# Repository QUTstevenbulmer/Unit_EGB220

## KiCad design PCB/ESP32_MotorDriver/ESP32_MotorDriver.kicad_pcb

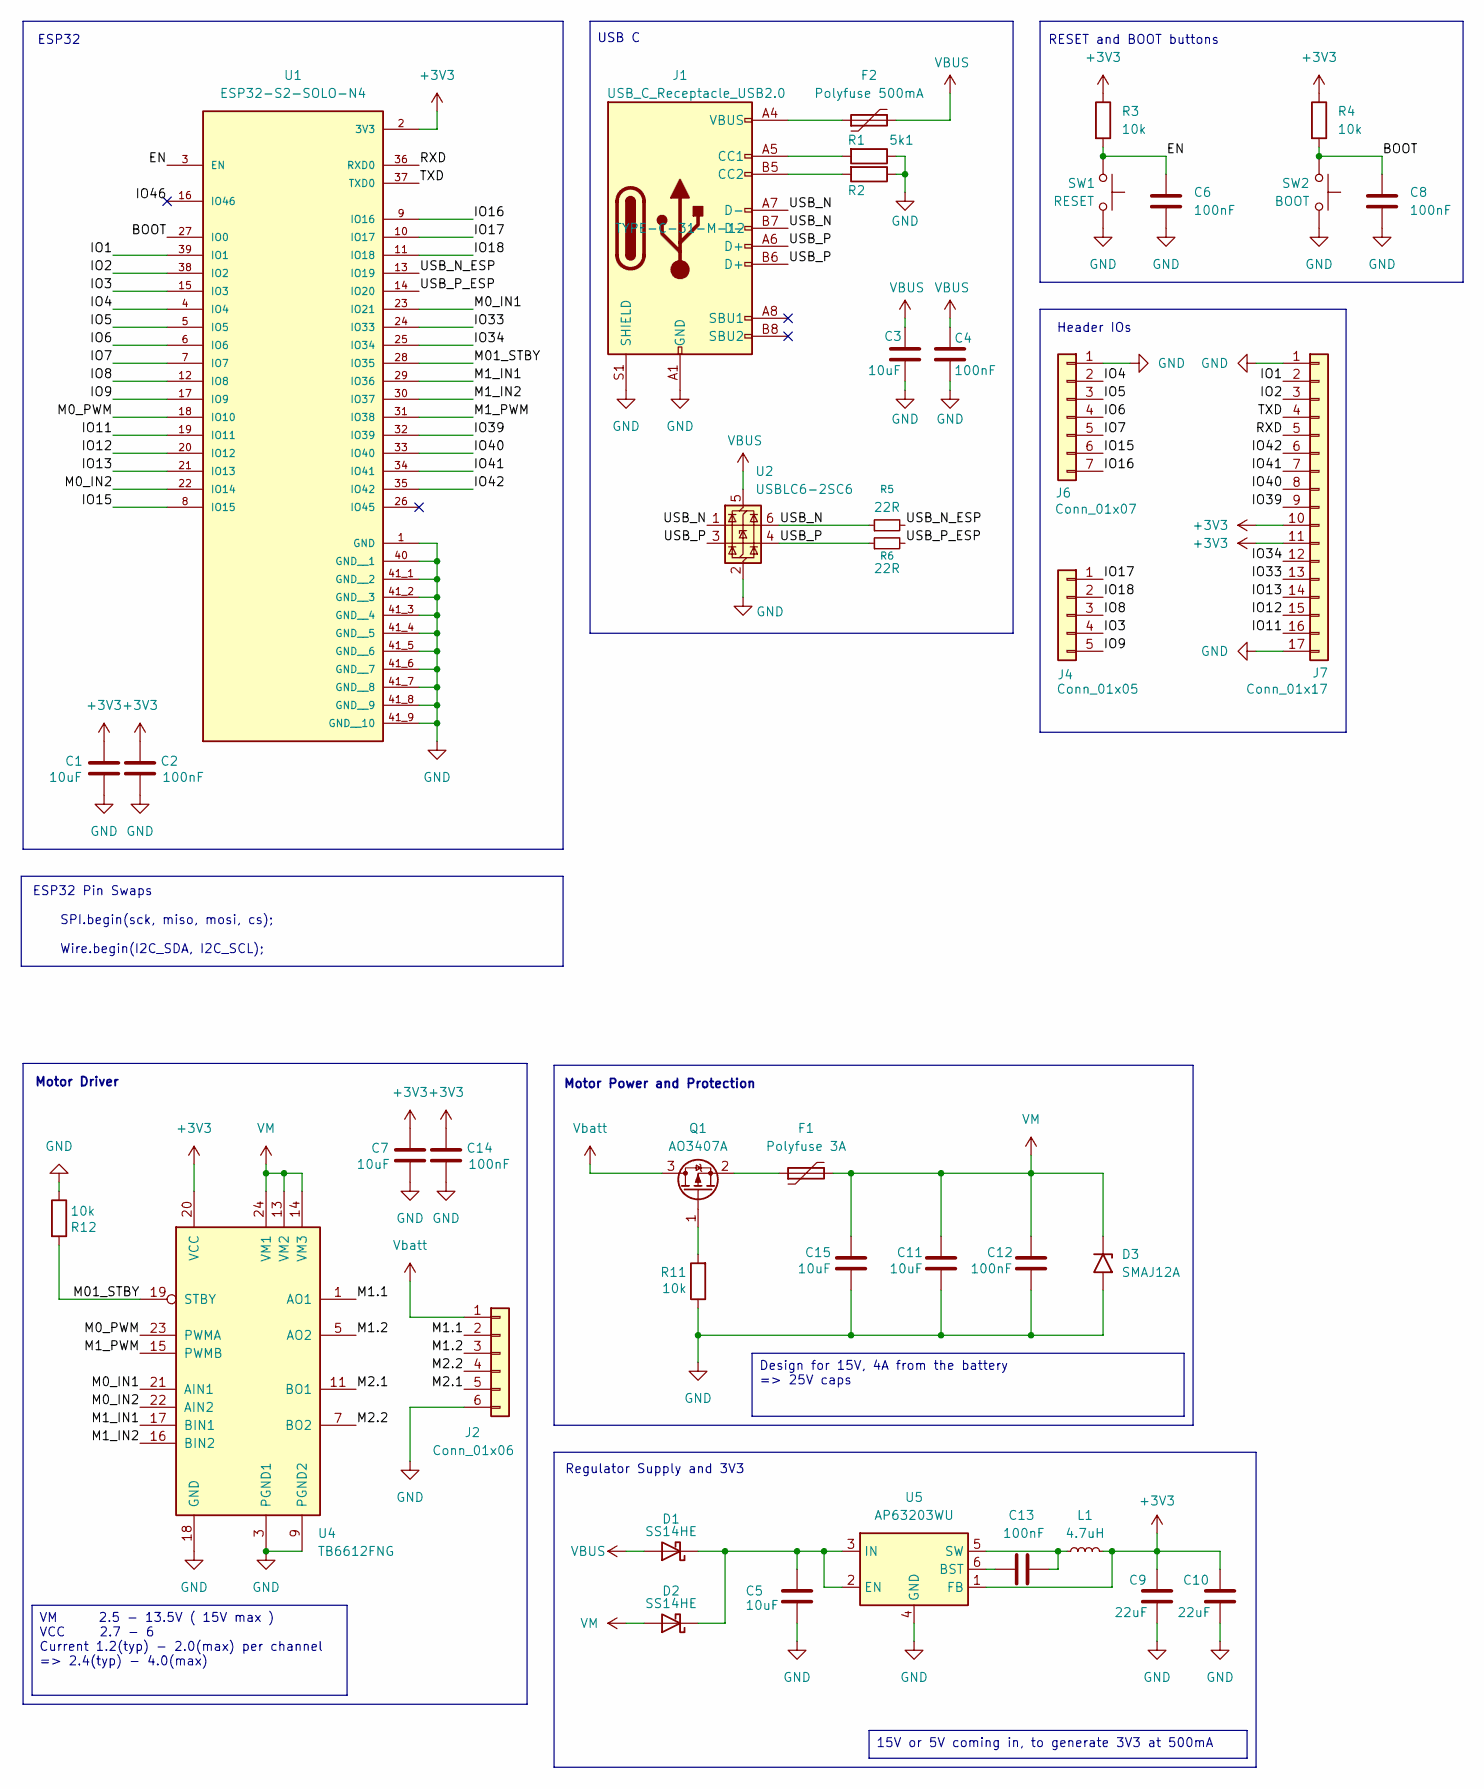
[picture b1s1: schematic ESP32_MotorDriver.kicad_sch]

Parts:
C1, C5, C7, C15: 10uF; C_0805_2012Metric_Pad1.18x1.45mm_HandSolder
C2, C6, C8, C14: 100nF; C_0402_1005Metric_Pad0.74x0.62mm_HandSolder
C3: 10uF; C_0805_2012Metric_Pad1.18x1.45mm_HandSolder; LCSC Part # C15850
C4: 100nF; C_0402_1005Metric_Pad0.74x0.62mm_HandSolder; LCSC Part # C15850
C9, C10: 22uF; C_0805_2012Metric_Pad1.18x1.45mm_HandSolder
C11: 10uF; C_0805_2012Metric_Pad1.18x1.45mm_HandSolder; LCSC PN C3902158
C12, C13: 100nF; C_0402_1005Metric_Pad0.74x0.62mm_HandSolder; LCSC PN C105882
D1, D2: SS14HE; D_SOD-323HE_SS14HE
D3: SMAJ12A; D_SMA
F1: Polyfuse 3A; Fuse_1812_4532Metric_Pad1.30x3.40mm_HandSolder
F2: Polyfuse 500mA; Fuse_0805_2012Metric_Pad1.15x1.40mm_HandSolder
J1: USB_C_Receptacle_USB2.0; USB_C_Receptacle_HRO_TYPE-C-31-M-12; LCSC Part # C165948
J2: Conn_01x06; PinHeader_1x06_P2.54mm_Vertical
J4: Conn_01x05; PinHeader_1x05_P2.54mm_Vertical
J6: Conn_01x07; PinHeader_1x07_P2.54mm_Vertical
J7: Conn_01x17; PinHeader_1x17_P2.54mm_Vertical
L1: 4.7uH; L_1008_2520Metric_Pad1.43x2.20mm_HandSolder
Q1: AO3407A; SOT-23
R1, R2: 5k1; R_0402_1005Metric_Pad0.72x0.64mm_HandSolder
R3, R4: 10k; R_0402_1005Metric_Pad0.72x0.64mm_HandSolder; LCSC Part # C100047
R5, R6: 22R; R_0402_1005Metric_Pad0.72x0.64mm_HandSolder
R11, R12: 10k; R_0402_1005Metric_Pad0.72x0.64mm_HandSolder; LCSC PN C851816
SW1: RESET; Switch SMD STO
SW2: BOOT; Switch SMD STO; LCSC_PN C25168823
U1: ESP32-S2-SOLO-N4; XCVR_ESP32-S2-SOLO-N4; PARTREV 1.6
U2: USBLC6-2SC6; SOT-23-6
U4: TB6612FNG; SSOP-24_5.3x8.2mm_P0.65mm; LCSC PN C141517
U5: AP63203WU; TSOT-23-6

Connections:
+3V3: C1.1, C2.1, C7.1, C9.1, C10.1, C14.1, J7.10, J7.11, L1.2, R3.1, R4.1, U1.2 (3V3), U4.20 (VCC), U5.1 (FB)
/BOOT: C8.1, R4.2, SW2.1, U1.27 (IO0)
/EN: C6.1, R3.2, SW1.1, U1.3 (EN)
/IO1: J7.2, U1.39 (IO1)
/IO2: J7.3, U1.38 (IO2)
/IO3: J4.4, U1.15 (IO3)
/IO4: J6.2, U1.4 (IO4)
/IO5: J6.3, U1.5 (IO5)
/IO6: J6.4, U1.6 (IO6)
/IO7: J6.5, U1.7 (IO7)
/IO8: J4.3, U1.12 (IO8)
/IO9: J4.5, U1.17 (IO9)
/IO11: J7.16, U1.19 (IO11)
/IO12: J7.15, U1.20 (IO12)
/IO13: J7.14, U1.21 (IO13)
/IO15: J6.6, U1.8 (IO15)
/IO16: J6.7, U1.9 (IO16)
/IO17: J4.1, U1.10 (IO17)
/IO18: J4.2, U1.11 (IO18)
/IO33: J7.13, U1.24 (IO33)
/IO34: J7.12, U1.25 (IO34)
/IO39: J7.9, U1.32 (IO39)
/IO40: J7.8, U1.33 (IO40)
/IO41: J7.7, U1.34 (IO41)
/IO42: J7.6, U1.35 (IO42)
/IO46: U1.16 (IO46)
/M0_IN1: U1.23 (IO21), U4.21 (AIN1)
/M0_IN2: U1.22 (IO14), U4.22 (AIN2)
/M0_PWM: U1.18 (IO10), U4.23 (PWMA)
/M1.1: J2.2, U4.1 (AO1), U4.2 (AO1)
/M1.2: J2.3, U4.5 (AO2), U4.6 (AO2)
/M1_IN1: U1.29 (IO36), U4.17 (BIN1)
/M1_IN2: U1.30 (IO37), U4.16 (BIN2)
/M1_PWM: U1.31 (IO38), U4.15 (PWMB)
/M01_STBY: R12.2, U1.28 (IO35), U4.19 (STBY)
/M2.1: J2.5, U4.11 (BO1), U4.12 (BO1)
/M2.2: J2.4, U4.7 (BO2), U4.8 (BO2)
/RXD: J7.5, U1.36 (RXD0)
/TXD: J7.4, U1.37 (TXD0)
/USB_N: J1.A7 (D-), J1.B7 (D-), R5.1, U2.1 (I/O1), U2.6 (I/O1)
/USB_N_ESP: R5.2, U1.13 (IO19)
/USB_P: J1.A6 (D+), J1.B6 (D+), R6.1, U2.3 (I/O2), U2.4 (I/O2)
/USB_P_ESP: R6.2, U1.14 (IO20)
GND: C1.2, C2.2, C3.2, C4.2, C5.2, C6.2, C7.2, C8.2, C9.2, C10.2, C11.2, C12.2, C14.2, C15.2, D3.2 (A2), J1.A1 (GND), J1.A12 (GND), J1.B1 (GND), J1.B12 (GND), J1.S1 (SHIELD), J2.6, J6.1, J7.1, J7.17, R1.1, R2.1, R11.1, R12.1, SW1.2, SW2.2, U1.1 (GND), U1.40 (GND__1), U1.41_1 (GND__2), U1.41_2 (GND__3), U1.41_3 (GND__4), U1.41_4 (GND__5), U1.41_5 (GND__6), U1.41_6 (GND__7), U1.41_7 (GND__8), U1.41_8 (GND__9), U1.41_9 (GND__10), U2.2 (GND), U4.3 (PGND1), U4.4 (PGND1), U4.9 (PGND2), U4.10 (PGND2), U4.18 (GND), U5.4 (GND)
unnamed: C5.1, D1.1 (K), D2.1 (K), U5.2 (EN), U5.3 (IN)
unnamed: F2.1, J1.A4 (VBUS), J1.A9 (VBUS), J1.B4 (VBUS), J1.B9 (VBUS)
unnamed: J1.A5 (CC1), R1.2
unnamed: J1.B5 (CC2), R2.2
unnamed: Q1.1 (G), R11.2
unnamed: F1.1, Q1.2 (S)
unnamed: C13.1, U5.6 (BST)
unnamed: C13.2, L1.1, U5.5 (SW)
VBUS: C3.1, C4.1, D1.2 (A), F2.2, U2.5 (VBUS)
VM: C11.1, C12.1, C15.1, D2.2 (A), D3.1 (A1), F1.2, U4.13 (VM2), U4.14 (VM3), U4.24 (VM1)
Vbatt: J2.1, Q1.3 (D)

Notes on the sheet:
ESP32 Pin Swaps SPI.begin(sck, miso, mosi, cs); Wire.begin(I2C_SDA, I2C_SCL);
Regulator Supply and 3V3
Header IOs
Motor Driver
RESET and BOOT buttons
USB C
ESP32
Motor Power and Protection
15V or 5V coming in, to generate 3V3 at 500mA
Design for 15V, 4A from the battery => 25V caps
VM 2.5 - 13.5V ( 15V max ) VCC 2.7 - 6 Current 1.2(typ) - 2.0(max) per channel => 2.4(typ) - 4.0(max)

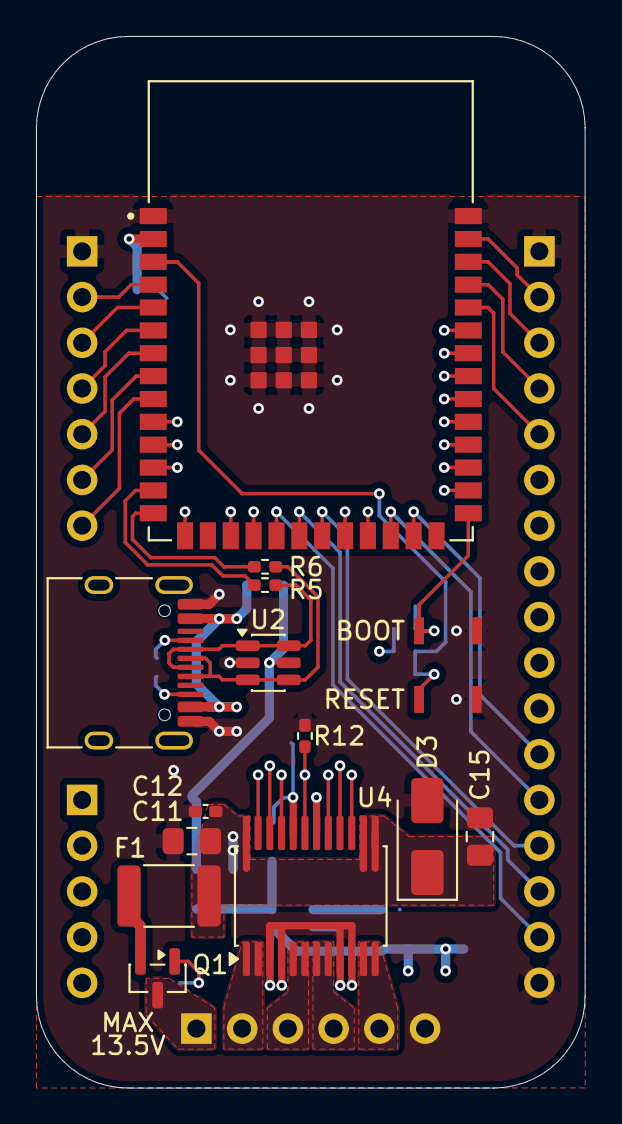
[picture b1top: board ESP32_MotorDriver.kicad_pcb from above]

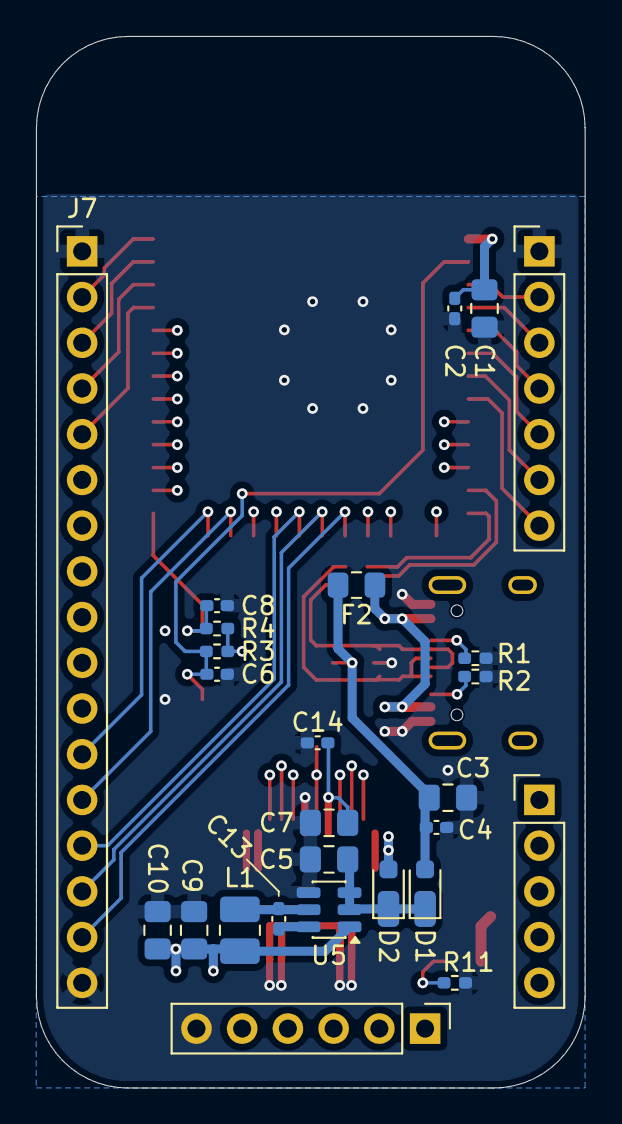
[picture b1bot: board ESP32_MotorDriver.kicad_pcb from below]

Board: 4 copper layers, 30.5 x 58.4 mm, 41 parts (26 on the bottom side), 54 nets.

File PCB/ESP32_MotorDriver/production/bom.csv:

Designator,Footprint,Quantity,Value,LCSC Part #
"C1, C15, C5, C7",0805,4,10uF,
"C10, C9",0805,2,22uF,
C11,0805,1,10uF,C3902158
"C12, C13",0402,2,100nF,C105882
"C14, C2, C6, C8",0402,4,100nF,
C3,0805,1,10uF,C15850
C4,0402,1,100nF,C15850
"D1, D2",D_SOD-323F,2,SS14HE,
D3,D_SMA,1,SMAJ12A,
F1,1812,1,Polyfuse 3A,
F2,0805,1,Polyfuse 500mA,
J1,USB_C_Receptacle_HRO_TYPE-C-31-M-12,1,USB_C_Receptacle_USB2.0,C165948
J2,PinHeader_1x06_P2.54mm_Vertical,1,Conn_01x06,
J4,PinHeader_1x05_P2.54mm_Vertical,1,Conn_01x05,
J6,PinHeader_1x07_P2.54mm_Vertical,1,Conn_01x07,
J7,PinHeader_1x17_P2.54mm_Vertical,1,Conn_01x17,
L1,1008,1,4.7uH,
Q1,SOT-23,1,AO3407A,
"R1, R2",0402,2,5k1,
"R11, R12",0402,2,10k,C851816
"R3, R4",0402,2,10k,C100047
"R5, R6",0402,2,22R,
SW1,Switch SMD STO,1,RESET,
SW2,Switch SMD STO,1,BOOT,
U1,XCVR_ESP32-S2-SOLO-N4,1,ESP32-S2-SOLO-N4,
U2,SOT-23-6,1,USBLC6-2SC6,
U4,SSOP-24_5.3x8.2mm_P0.65mm,1,TB6612FNG,C141517
U5,TSOT-23-6,1,AP63203WU,

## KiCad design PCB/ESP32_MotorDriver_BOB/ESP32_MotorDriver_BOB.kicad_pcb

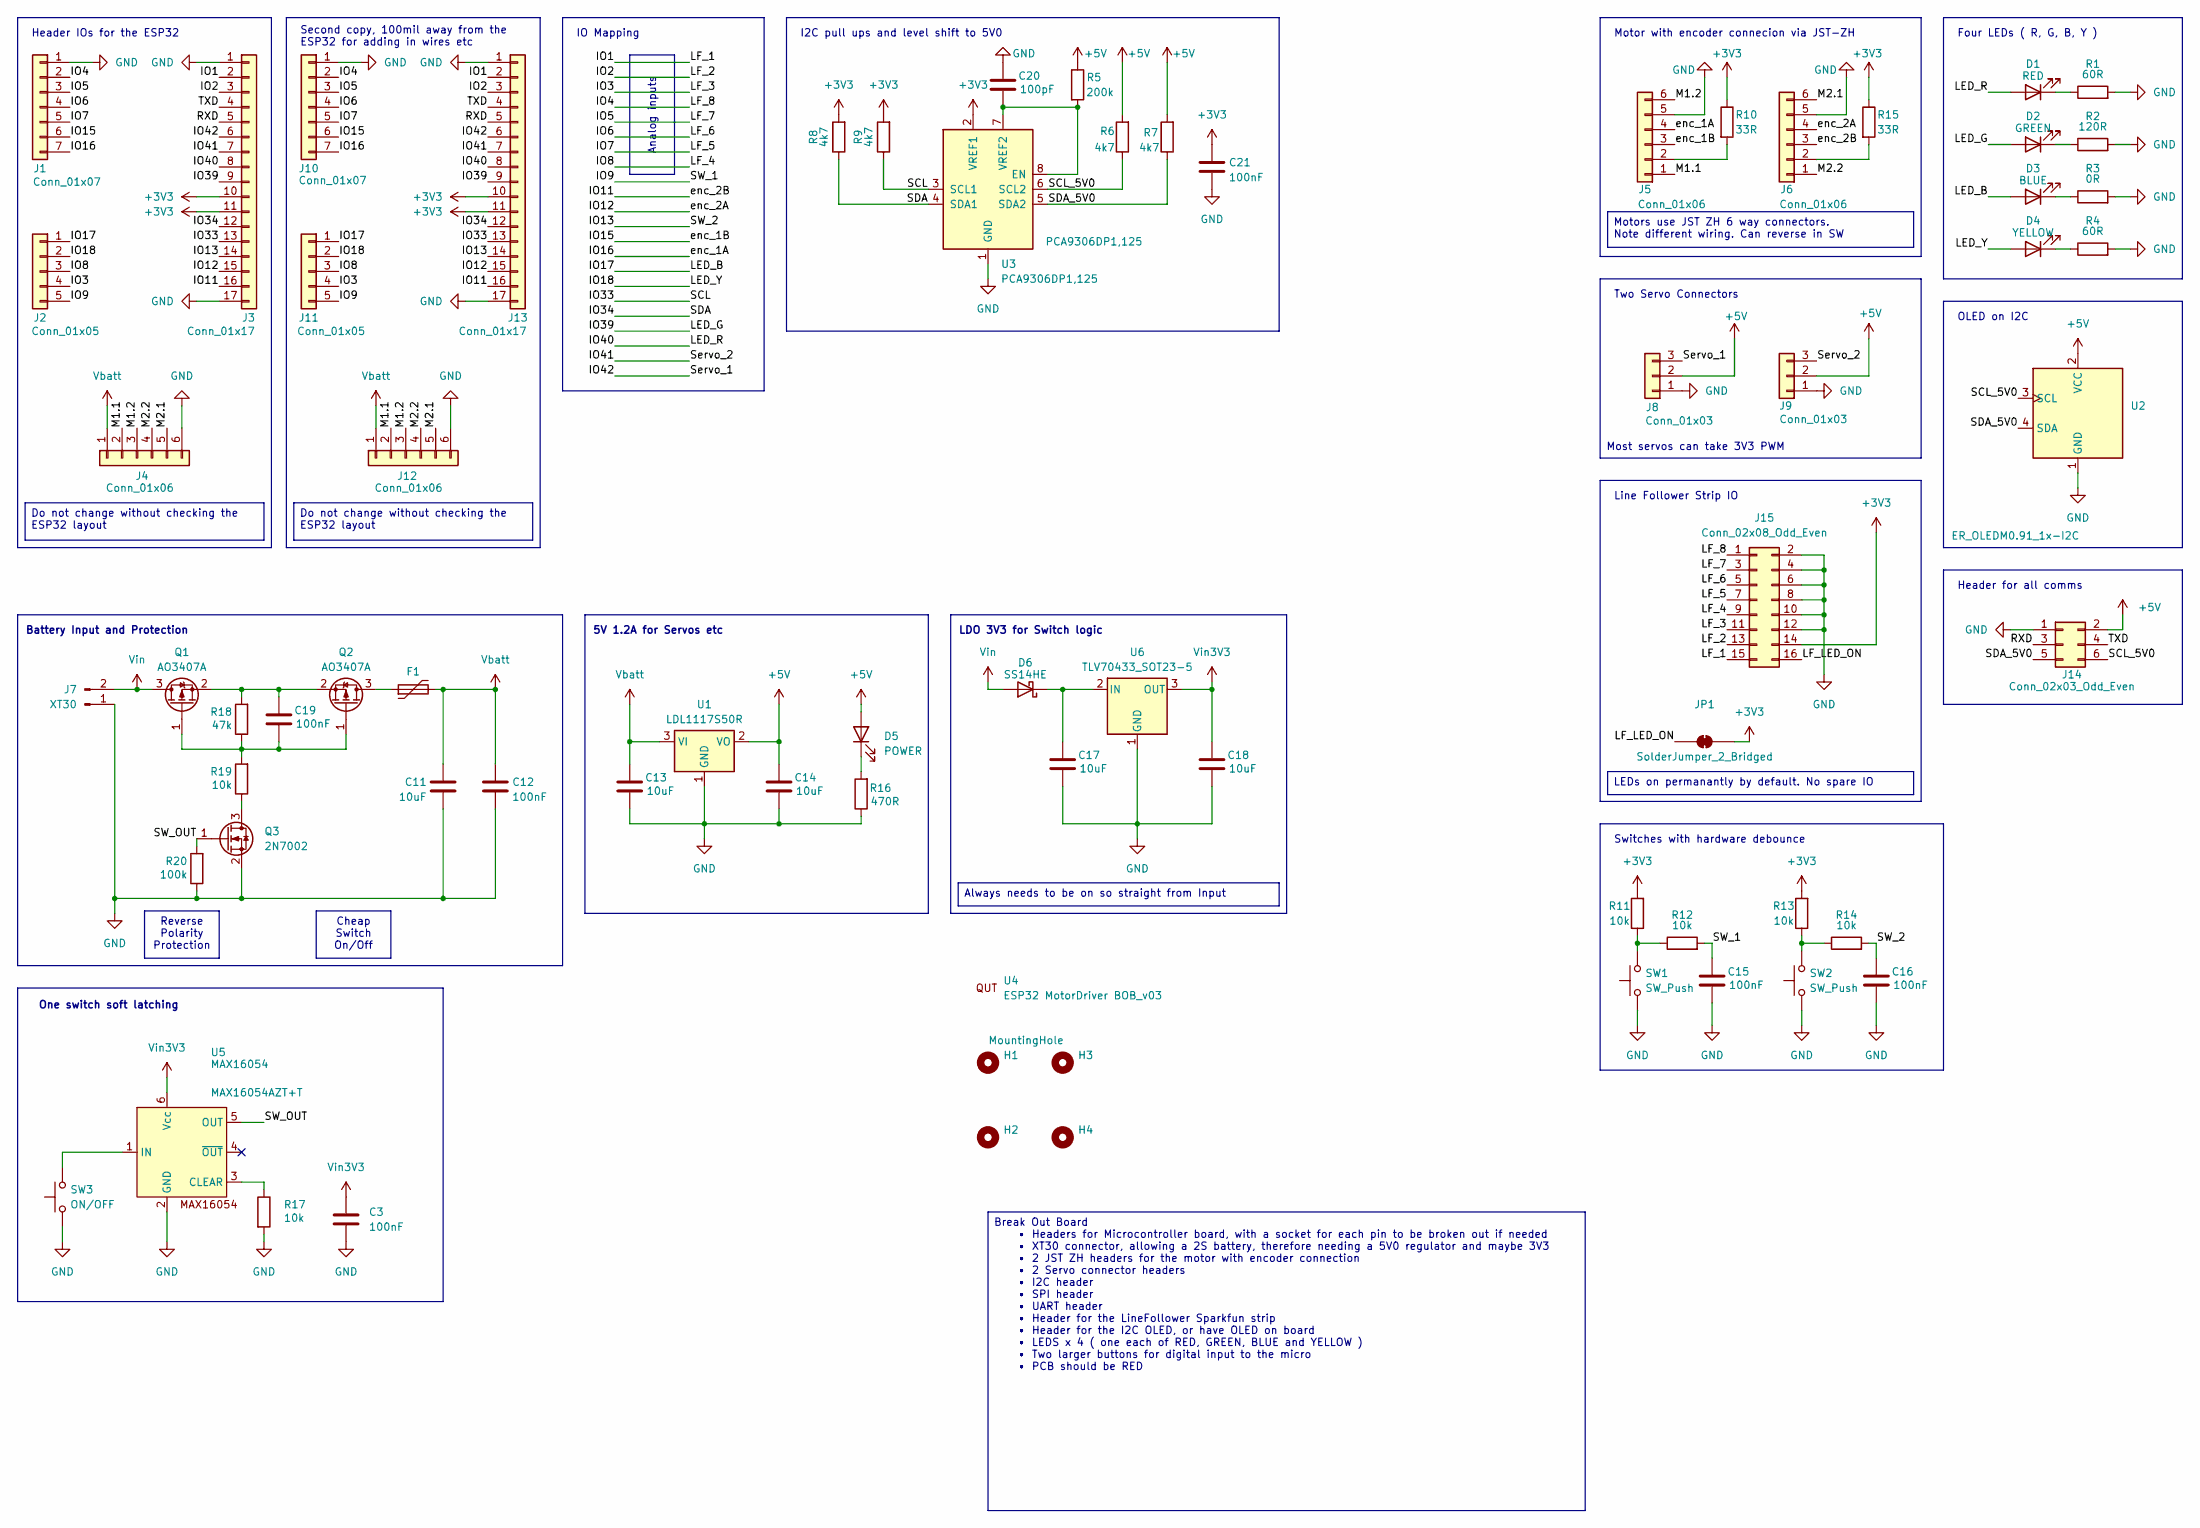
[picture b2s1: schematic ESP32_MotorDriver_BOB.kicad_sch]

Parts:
C3, C12, C15, C16, C19, C21: 100nF; C_0402_1005Metric_Pad0.74x0.62mm_HandSolder
C11, C13, C14, C17, C18: 10uF; C_0805_2012Metric_Pad1.18x1.45mm_HandSolder
C20: 100pF; C_0402_1005Metric_Pad0.74x0.62mm_HandSolder
D1: RED; LED_1206_3216Metric_Pad1.42x1.75mm_HandSolder
D2: GREEN; LED_1206_3216Metric_Pad1.42x1.75mm_HandSolder
D3: BLUE; LED_1206_3216Metric_Pad1.42x1.75mm_HandSolder
D4: YELLOW; LED_1206_3216Metric_Pad1.42x1.75mm_HandSolder
D5: POWER; LED_0805_2012Metric_Pad1.15x1.40mm_HandSolder
D6: SS14HE; D_SOD-323HE_SS14HE
F1: PTC RESET FUSE 16V 2.5A 1812; Fuse_1812_4532Metric_Pad1.30x3.40mm_HandSolder
H1, H2, H3, H4: MountingHole; MountingHole_3.2mm_M3
J1, J10: Conn_01x07; PinSocket_1x07_P2.54mm_Vertical
J2, J11: Conn_01x05; PinSocket_1x05_P2.54mm_Vertical
J3, J13: Conn_01x17; PinSocket_1x17_P2.54mm_Vertical
J4, J12: Conn_01x06; PinSocket_1x06_P2.54mm_Vertical
J5, J6: Conn_01x06; JST_ZH_S6B-ZR-SM4A-TF_1x06-1MP_P1.50mm_Horizontal
J7: XT30; AMASS_XT30PW-M_1x02_P2.50mm_Horizontal
J8, J9: Conn_01x03; PinHeader_1x03_P2.54mm_Vertical
J14: Conn_02x03_Odd_Even; PinHeader_2x03_P2.54mm_Vertical
J15: Conn_02x08_Odd_Even; PinHeader_2x08_P2.54mm_Vertical
JP1: SolderJumper_2_Bridged; SolderJumper-2_P1.3mm_Bridged_RoundedPad1.0x1.5mm
Q1, Q2: AO3407A; SOT-23
Q3: 2N7002; SOT-23
R1, R4: 60R; R_0402_1005Metric_Pad0.72x0.64mm_HandSolder
R2: 120R; R_0402_1005Metric_Pad0.72x0.64mm_HandSolder
R3: 0R; R_0402_1005Metric_Pad0.72x0.64mm_HandSolder
R5: 200k; R_0402_1005Metric_Pad0.72x0.64mm_HandSolder
R6, R7, R8, R9: 4k7; R_0402_1005Metric_Pad0.72x0.64mm_HandSolder
R10, R15: 33R; R_0402_1005Metric_Pad0.72x0.64mm_HandSolder
R11, R12, R13, R14, R17, R19: 10k; R_0402_1005Metric_Pad0.72x0.64mm_HandSolder
R16: 470R; R_0402_1005Metric_Pad0.72x0.64mm_HandSolder
R18: 47k; R_0402_1005Metric_Pad0.72x0.64mm_HandSolder
R20: 100k; R_0402_1005Metric_Pad0.72x0.64mm_HandSolder
SW1, SW2: SW_Push; SW_SPST_EVQP0
SW3: ON/OFF; SW_SPST_EVQP0
U1: LDL1117S50R; SOT-223-3_TabPin2
U2: ER_OLEDM0.91_1x-I2C
U3: PCA9306DP1,125; VSSOP-8_3x3mm_P0.65mm
U4: ESP32 MotorDriver BOB_v03; logo_QUT
U5: MAX16054; SOT-23-6
U6: TLV70433_SOT23-5; SOT-23-5

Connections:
+3V3: C21.1, J3.10, J3.11, J13.10, J13.11, J15.14, JP1.2 (B), R8.2, R9.2, R10.1, R11.2, R13.2, R15.1, U3.2 (VREF1)
+5V: C14.1, D5.2 (A), J8.2, J9.2, J14.2, R5.1, R6.2, R7.2, U1.2 (VO), U2.2 (VCC)
/IO1: J3.2, J13.2, J15.15
/IO2: J3.3, J13.3, J15.13
/IO3: J2.4, J11.4, J15.11
/IO4: J1.2, J10.2, J15.1
/IO5: J1.3, J10.3, J15.3
/IO6: J1.4, J10.4, J15.5
/IO7: J1.5, J10.5, J15.7
/IO8: J2.3, J11.3, J15.9
/IO9: C15.1, J2.5, J11.5, R12.2
/IO11: J3.16, J6.3, J13.16
/IO12: J3.15, J6.4, J13.15
/IO13: C16.1, J3.14, J13.14, R14.2
/IO15: J1.6, J5.3, J10.6
/IO16: J1.7, J5.4, J10.7
/IO17: D3.2 (A), J2.1, J11.1
/IO18: D4.2 (A), J2.2, J11.2
/IO33: J3.13, J13.13, R9.1, U3.3 (SCL1)
/IO34: J3.12, J13.12, R8.1, U3.4 (SDA1)
/IO39: D2.2 (A), J3.9, J13.9
/IO40: D1.2 (A), J3.8, J13.8
/IO41: J3.7, J9.3, J13.7
/IO42: J3.6, J8.3, J13.6
/LF_LED_ON: J15.16, JP1.1 (A)
/M1.1: J4.2, J5.1, J12.2
/M1.2: J4.3, J5.6, J12.3
/M2.1: J4.5, J6.6, J12.5
/M2.2: J4.4, J6.1, J12.4
/RXD: J3.5, J13.5, J14.3
/SCL_5V0: J14.6, R6.1, U2.3 (SCL), U3.6 (SCL2)
/SDA_5V0: J14.5, R7.1, U2.4 (SDA), U3.5 (SDA2)
/SW_OUT: Q3.1 (G), R20.2, U5.5 (OUT)
/TXD: J3.4, J13.4, J14.4
GND: C3.2, C11.2, C12.2, C13.2, C14.2, C15.2, C16.2, C17.2, C18.2, C20.1, C21.2, J1.1, J3.1, J3.17, J4.6, J5.5, J6.5, J7.1, J8.1, J9.1, J10.1, J12.6, J13.1, J13.17, J14.1, J15.2, J15.4, J15.6, J15.8, J15.10, J15.12, Q3.2 (S), R1.2, R2.2, R3.2, R4.2, R16.1, R17.2, R20.1, SW1.1, SW2.1, SW3.1, U1.1 (GND), U2.1 (GND), U3.1 (GND), U5.2 (GND), U6.1 (GND)
unnamed: D1.1 (K), R1.1
unnamed: D2.1 (K), R2.1
unnamed: D3.1 (K), R3.1
unnamed: D4.1 (K), R4.1
unnamed: D5.1 (K), R16.2
unnamed: C17.1, D6.1 (K), U6.2 (IN)
unnamed: J5.2, R10.2
unnamed: J6.2, R15.2
unnamed: C19.2, Q1.1 (G), Q2.1 (G), R18.1, R19.2
unnamed: C19.1, Q1.2 (S), Q2.2 (S), R18.2
unnamed: F1.1, Q2.3 (D)
unnamed: Q3.3 (D), R19.1
unnamed: R11.1, R12.1, SW1.2
unnamed: R13.1, R14.1, SW2.2
unnamed: C20.2, R5.2, U3.7 (VREF2), U3.8 (EN)
unnamed: R17.1, U5.3 (CLEAR)
unnamed: SW3.2, U5.1 (IN)
Vbatt: C11.1, C12.1, C13.1, F1.2, J4.1, J12.1, U1.3 (VI)
Vin: D6.2 (A), J7.2, Q1.3 (D)
Vin3V3: C3.1, C18.1, U5.6 (Vcc), U6.3 (OUT)

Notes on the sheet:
Line Follower Strip IO
Header IOs for the ESP32
Most servos can take 3V3 PWM
Two Servo Connectors
Battery Input and Protection
Switches with hardware debounce
5V 1.2A for Servos etc
OLED on I2C
LDO 3V3 for Switch logic
Second copy, 100mil away from the ESP32 for adding in wires etc
Motor with encoder connecion via JST-ZH
Four LEDs ( R, G, B, Y )
Header for all comms
One switch soft latching
IO Mapping
I2C pull ups and level shift to 5V0
Cheap Switch On/Off
Break Out Board • Headers for Microcontroller board, with a socket for each pin to be broken out if needed • XT30 connector, allowing a 2S battery, therefore needing a 5V0 regulator and maybe 3V3 • 2 JST ZH headers for the motor with encoder connection • 2 Servo connector headers • I2C header • SPI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
Do not change without checking the ESP32 layout
LEDs on permanantly by default. No spare IO
Reverse Polarity Protection
Always needs to be on so straight from Input
Motors use JST ZH 6 way connectors. Note different wiring. Can reverse in SW
Analog inputs

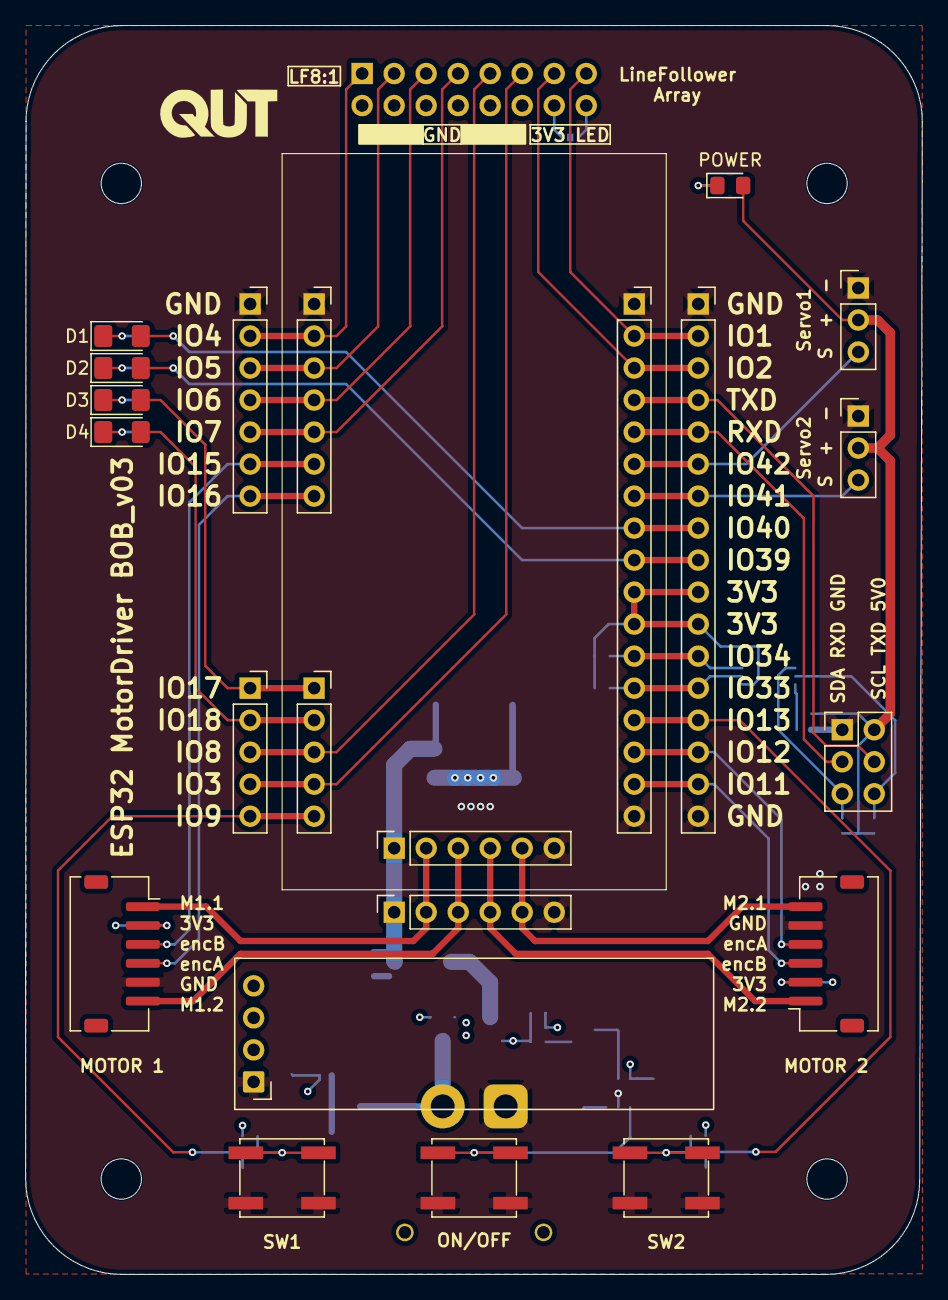
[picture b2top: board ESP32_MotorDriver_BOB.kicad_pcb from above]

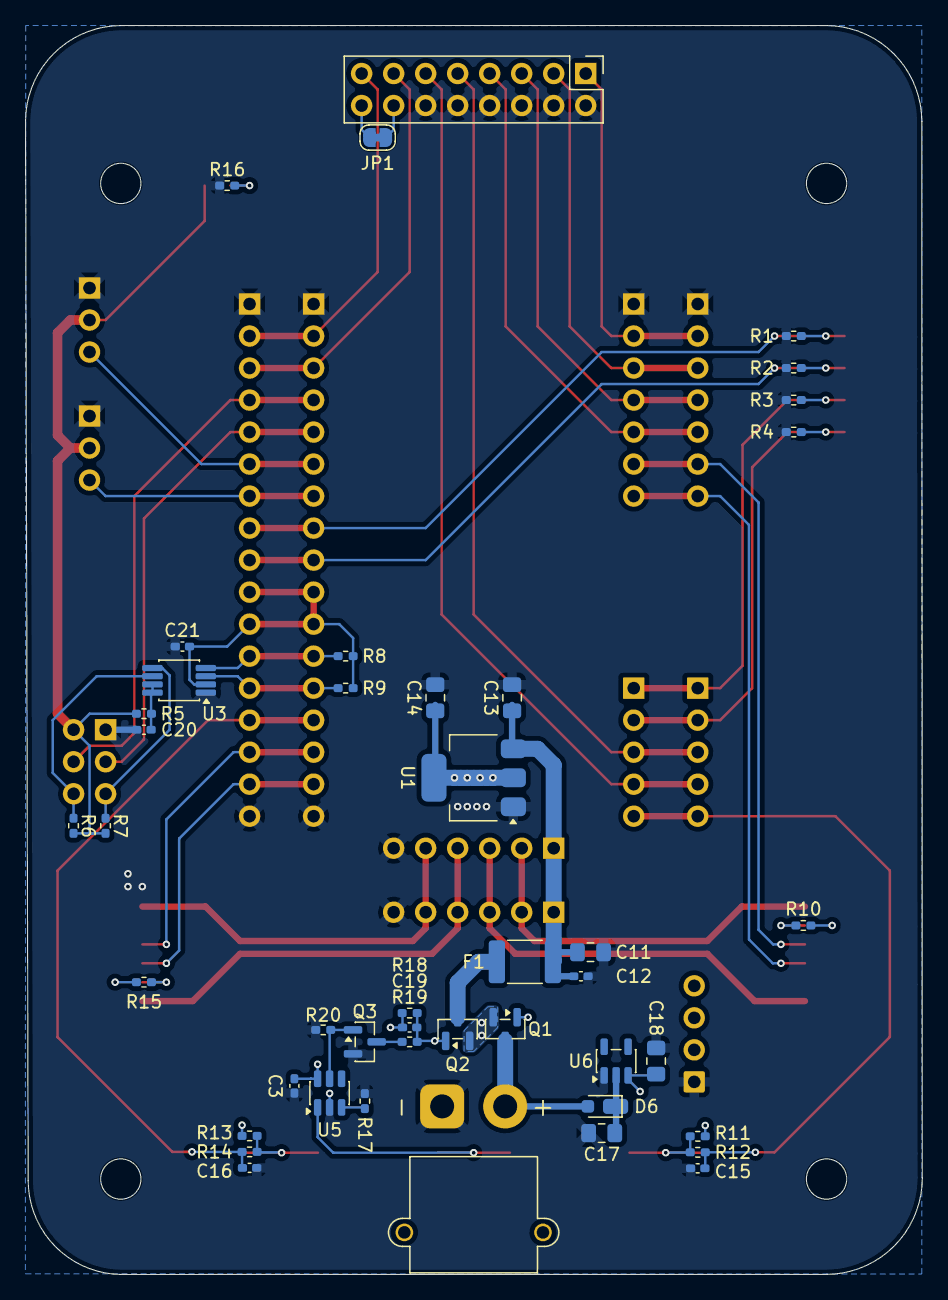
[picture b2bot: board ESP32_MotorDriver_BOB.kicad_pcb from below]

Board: 4 copper layers, 71.2 x 99.1 mm, 71 parts (44 on the bottom side), 55 nets.

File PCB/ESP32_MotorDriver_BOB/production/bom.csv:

Designator,Footprint,Quantity,Value,LCSC Part #
"C11, C13, C14",0402,3,10uF,C3902158
"C12, C15, C16",0402,3,100nF,C105882
D1,1206,1,RED,
D2,1206,1,GREEN,
D3,1206,1,BLUE,
D4,1206,1,YELLOW,
F1,0805,1,Polyfuse 4A,C22368431
"J1, J10",PinSocket_1x07_P2.54mm_Vertical,2,Conn_01x07,
"J11, J2",PinSocket_1x05_P2.54mm_Vertical,2,Conn_01x05,
"J12, J4",PinSocket_1x06_P2.54mm_Vertical,2,Conn_01x06,
"J13, J3",PinSocket_1x17_P2.54mm_Vertical,2,Conn_01x17,
J14,PinHeader_2x03_P2.54mm_Vertical,1,Conn_02x03_Odd_Even,
J15,PinHeader_2x08_P2.54mm_Vertical,1,Conn_02x08_Odd_Even,
"J5, J6",JST_XH_S6B-XH-A_1x06_P2.50mm_Horizontal,2,Conn_01x06,
J7,AMASS_XT30PW-M_1x02_P2.50mm_Horizontal,1,XT30,C431092
"J8, J9",PinHeader_1x03_P2.54mm_Vertical,2,Conn_01x03,
Q1,SOT-23F_TOS,1,SSM3J338R_LF,C146352
"R1, R2, R3, R4",0402,4,150R,
R10,0402,1,10k,C851816
"R11, R12, R13, R14",0402,4,10k,
R5,0402,1,100k,
"R6, R7, R8, R9",0402,4,4k7,
"SW1, SW2",SW_SPST_EVQP0,2,SW_Push,
U1,SOT-223-3_TabPin2,1,LDL1117S50R,
U2,ER_OLEDM0.91_1x-I2C,1,ER_OLEDM0.91_1x-I2C,
U3,SO-8_3.9x4.9mm_P1.27mm,1,PCA9306D,
U4,logo_QUT,1,ESP32 MotorDriver BOB_v01,
